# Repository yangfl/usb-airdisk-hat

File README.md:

# USB AirDisk HAT

- [wiki](/wiki)

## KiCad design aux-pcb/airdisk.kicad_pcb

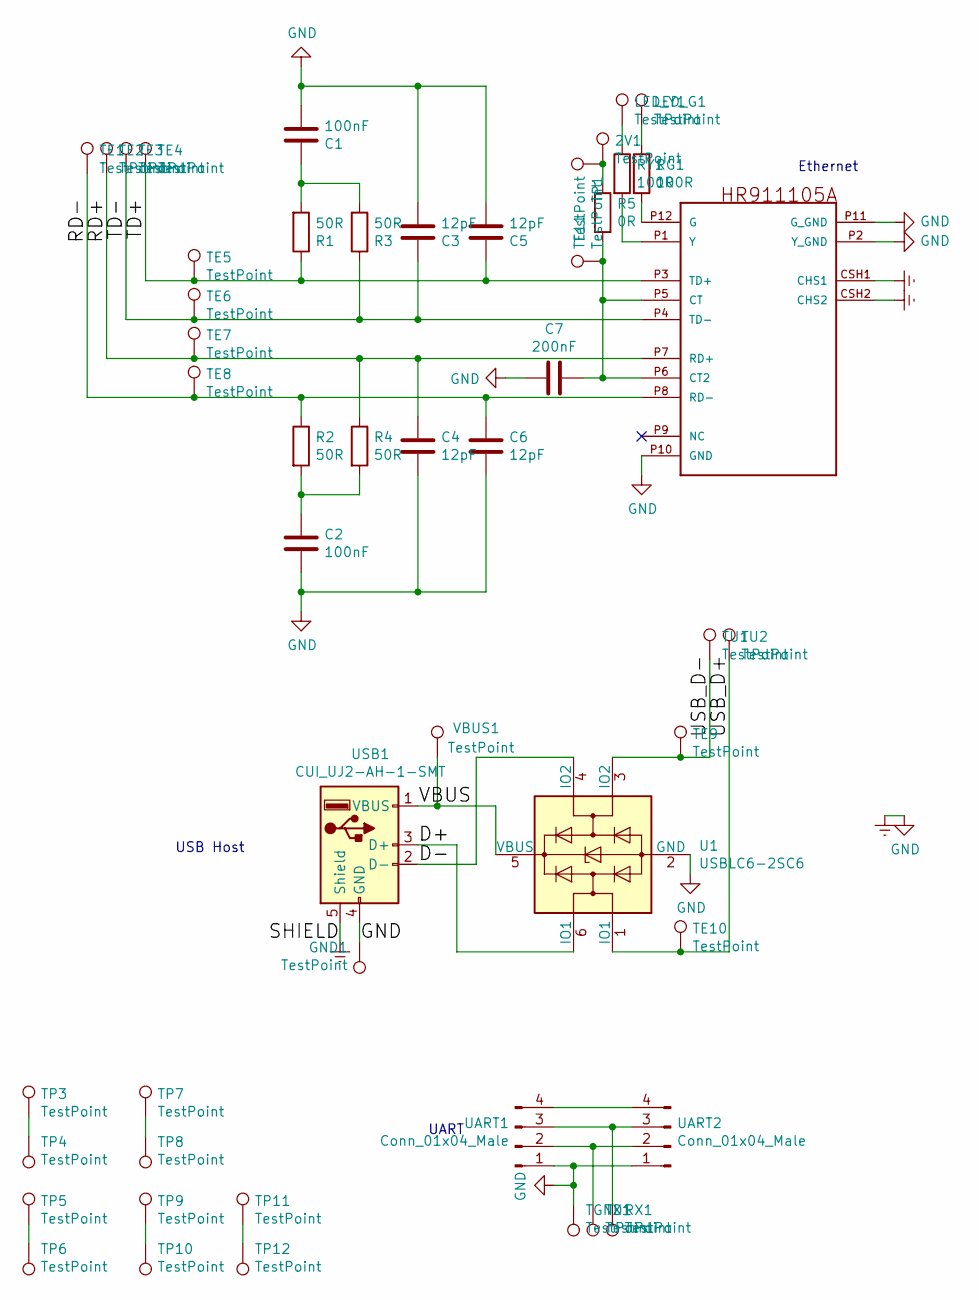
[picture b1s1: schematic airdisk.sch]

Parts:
2V1: TestPoint; TE_3-2199250-5
C1, C2: 100nF; C_0603_1608Metric_Pad1.05x0.95mm_HandSolder
C3, C4, C5, C6: 12pF; C_0603_1608Metric_Pad1.05x0.95mm_HandSolder
C7: 200nF; C_0603_1608Metric_Pad1.05x0.95mm_HandSolder
ETH1: HR961160C
GND1: TestPoint; TE_3-2199250-5
LED_G1: TestPoint; TestPoint_Pad_D1.5mm
LED_Y1: TestPoint; TestPoint_Pad_D1.5mm
R1, R2, R3, R4: 50R; R_0603_1608Metric_Pad1.05x0.95mm_HandSolder
R5: 0R; R_0402_1005Metric
RG1: 100R; R_0603_1608Metric_Pad1.05x0.95mm_HandSolder
RX1: TestPoint; TE_3-2199250-5
RY1: 100R; R_0603_1608Metric_Pad1.05x0.95mm_HandSolder
TE1, TE2, TE3, TE4: TestPoint; TE_3-2199250-5
TE5, TE6, TE7, TE8, TE9, TE10, TE11: TestPoint; SolderWirePad_1x01_Drill1mm
TGND1: TestPoint; TE_3-2199250-5
TP1, TP4, TP6, TP8, TP10, TP12: TestPoint; TestPoint_Pad_D1.5mm
TP3, TP5, TP7, TP9, TP11: TestPoint; TE_3-2199250-5
TU1, TU2: TestPoint; TE_3-2199250-5
TX1: TestPoint; TE_3-2199250-5
U1: USBLC6-2SC6; SOT-23-6
UART1: Conn_01x04_Male; PinHeader_1x04_P2.54mm_Vertical
UART2: Conn_01x04_Male; PinHeader_1x04_P2.54mm_Vertical_SMD_Pin1Left
USB1: CUI_UJ2-AH-1-SMT
VBUS1: TestPoint; TestPoint_Pad_D1.5mm

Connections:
/D+: U1.6 (IO1), USB1.3 (D+)
/D-: U1.4 (IO2), USB1.2 (D-)
/RD+: C4.1, ETH1.P7 (RD+), R4.1, TE2.1, TE7.1
/RD-: C6.1, ETH1.P8 (RD-), R2.1, TE1.1, TE8.1
/TD+: C5.1, ETH1.P3 (TD+), R1.1, TE4.1, TE5.1
/TD-: C3.1, ETH1.P4 (TD-), R3.1, TE3.1, TE6.1
/USB_D+: TE10.1, TU2.1, U1.1 (IO1)
/USB_D-: TE9.1, TU1.1, U1.3 (IO2)
/VBUS: U1.5 (VBUS), USB1.1 (VBUS), VBUS1.1
Earth: C1.2, C2.2, C3.2, C4.2, C5.2, C6.2, C7.2, ETH1.CSH1 (CHS1), ETH1.CSH2 (CHS2), ETH1.P2 (Y_GND), ETH1.P10 (GND), ETH1.P11 (G_GND), GND1.1, TGND1.1, U1.2 (GND), UART1.1, UART2.1, USB1.4 (GND), USB1.5 (Shield)
unnamed: 2V1.1, R5.1, TP1.1
unnamed: C1.1, R1.2, R3.2
unnamed: C2.1, R2.2, R4.2
unnamed: C7.1, ETH1.P5 (CT), ETH1.P6 (CT2), R5.2, TE11.1
unnamed: ETH1.P1 (Y), RY1.2
unnamed: ETH1.P12 (G), RG1.2
unnamed: LED_G1.1, RG1.1
unnamed: LED_Y1.1, RY1.1
unnamed: RX1.1, UART1.3, UART2.3
unnamed: TP3.1, TP4.1
unnamed: TP5.1, TP6.1
unnamed: TP7.1, TP8.1
unnamed: TP9.1, TP10.1
unnamed: TP11.1, TP12.1
unnamed: TX1.1, UART1.2, UART2.2
unnamed: UART1.4, UART2.4

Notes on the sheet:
Ethernet
USB Host
UART

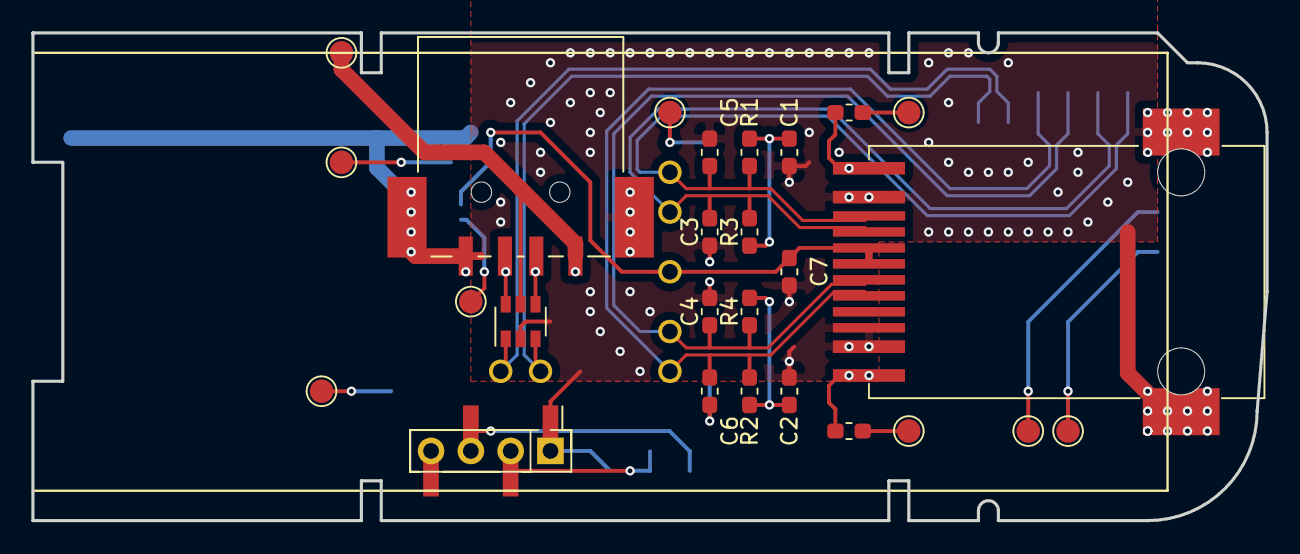
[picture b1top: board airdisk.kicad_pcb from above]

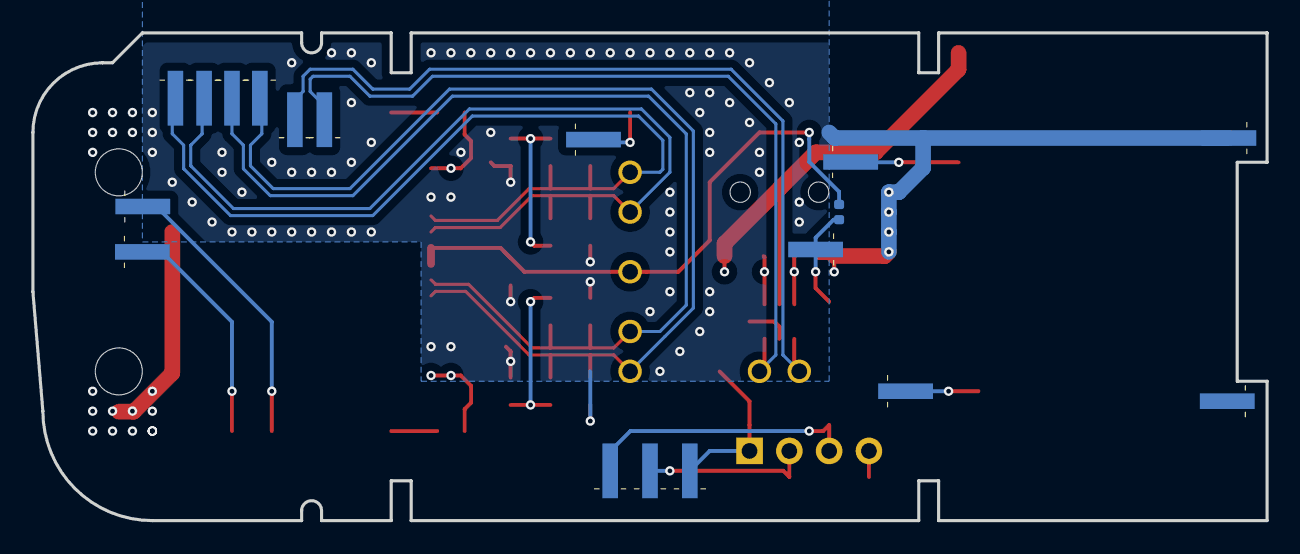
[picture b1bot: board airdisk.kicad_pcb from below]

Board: 2 copper layers, 78.7 x 31.1 mm, 51 parts (17 on the bottom side), 26 nets.

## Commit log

2019-06-24 add gpios defined
2019-07-09 add aux pcb
2019-07-09 update info
2019-07-12 update pcb
